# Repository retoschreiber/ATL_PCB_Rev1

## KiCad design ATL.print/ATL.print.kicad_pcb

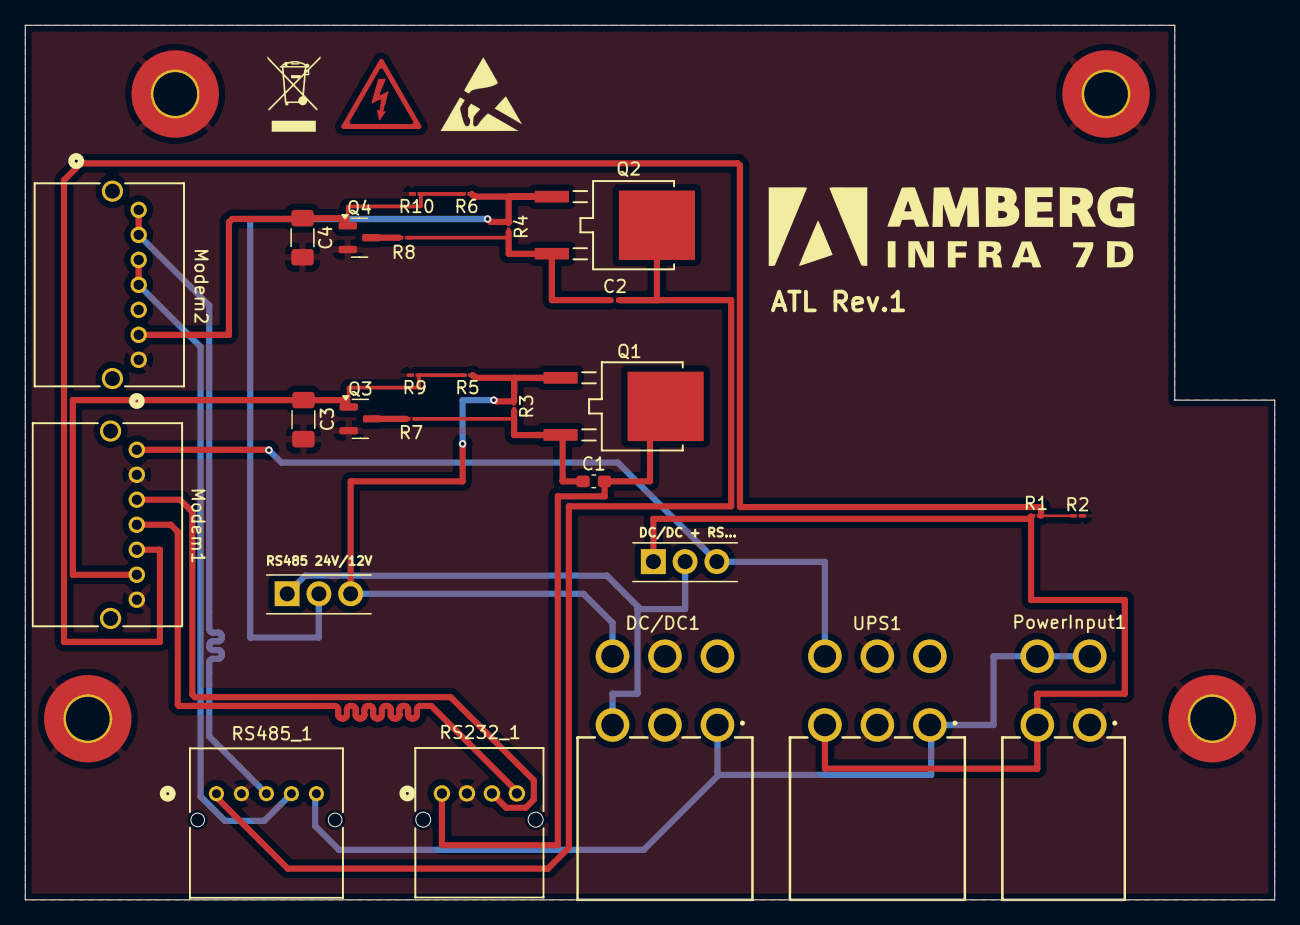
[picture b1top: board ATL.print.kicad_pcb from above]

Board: 2 copper layers, 100.0 x 70.0 mm, 27 parts (0 on the bottom side), 20 nets.

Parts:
C1: 10N; C_0603_1608Metric_Pad1.08x0.95mm_HandSolder
C2: 10N; C_0201_0603Metric_Pad0.64x0.40mm_HandSolder
C3, C4: 10U; C_1206_3216Metric_Pad1.33x1.80mm_HandSolder
DC/DC1: Conn_01x06_Pin; 64900629522
Jumper_DC1: Conn_01x03_Pin; TerminalBlock_Xinya_XY308-2.54-3P_1x03_P2.54mm_Horizontal
Jumper_RS1: Conn_01x03_Pin; TerminalBlock_Xinya_XY308-2.54-3P_1x03_P2.54mm_Horizontal
Modem1, Modem2: Conn_01x07_Pin; CONN7_K-2LFSN_JST
PowerInput1: Conn_01x04_Socket; 64900429522
Q1, Q2: NMOS; TO-252_D-PAK_AOS
Q3, Q4: NMOS; SOT-23
R1: 6k; R_01005_0402Metric_Pad0.57x0.30mm_HandSolder
R2: 10k; R_01005_0402Metric_Pad0.57x0.30mm_HandSolder
R3, R4: 47k; R_01005_0402Metric_Pad0.57x0.30mm_HandSolder
R5, R6, R9, R10: 220k; R_01005_0402Metric_Pad0.57x0.30mm_HandSolder
R7, R8: 100k; R_01005_0402Metric_Pad0.57x0.30mm_HandSolder
RS232_1: Conn_01x04_Socket; CONN4_S04B-PASK_JST
RS485_1: Conn_01x04_Socket; CONN_S05B-PASK-2_JST
UPS1: Conn_01x06_Pin; 64900629522

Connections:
Earth: DC/DC1.1, PowerInput1.3, PowerInput1.4, RS485_1.5, UPS1.1
Ex_Plus: Jumper_DC1.1, PowerInput1.2, R1.1, UPS1.3
GND: C3.2, C4.2, DC/DC1.2, DC/DC1.5, Modem1.2, Modem1.7, Modem2.7, PowerInput1.1, Q3.2 (S), Q4.2 (S), R2.2, R9.2, R10.2, RS232_1.2, RS485_1.2, UPS1.2, UPS1.5
unnamed: Jumper_RS1.2, Q2.1 (D), R4.1, R6.1
unnamed: C1.2, Q1.2 (G), R3.2, R7.2
unnamed: C2.2, Q2.2 (G), R4.2, R8.2
unnamed: Q3.3 (D), R7.1
unnamed: Q4.3 (D), R8.1
Plus_13.5: DC/DC1.6, Jumper_RS1.3, Q1.1 (D), R3.1, R5.1
Plus_24: Jumper_DC1.3, Modem1.1, UPS1.6
Plus_DC24: DC/DC1.3, Jumper_DC1.2, Jumper_RS1.1
RS232_Plus: C1.1, Q1.3 (S), RS232_1.1
RS485_Plus: C2.1, Q2.3 (S), RS485_1.1
RX: Modem1.4, RS232_1.4
R/D+: Modem2.1, Modem2.2, RS485_1.3
R/D-: Modem2.3, Modem2.4, RS485_1.4
Signal_ExternPower: Modem1.5, R1.2, R2.1
Switch_RS232: C3.1, Modem1.6, Q3.1 (G), R5.2, R9.1
Switch_RS485: C4.1, Modem2.6, Q4.1 (G), R6.2, R10.1
TX: Modem1.3, RS232_1.3

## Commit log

2025-02-25 Initial Checkin
2025-02-25 Erster Check IN
